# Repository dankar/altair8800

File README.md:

altair8800
==========

What is this?
-------------

What started as a Intel 8080 emulator turned into a Altair 8800 emulator with associated hardware for a front panel.

An updated version of this project is available at https://github.com/dankar/nanoaltair8800

Building
--------

The build for Arduino Uno is the most up to date. It should work to run "./build" and then "make && upload" in the arduino folder to compile and program.

arduino-mk is used by the makefile.

The code will look for certain files on the SD card. "88dskrom.bin" is a disk bootloader which will be loaded to offset 0xff00 in memory. "disk1.bin" and "disk2.bin" will be used by the 88-DCDD emulator and will act as disk 1 and disk 2 respectively.

Completeness
------------

Passes Kelly Smith test and cputest.com. Runs CP/M and all kinds of BASIC I could find. Altair DOS not working for some reason (complains about insufficient memory). Support for 88-DCDD. No tape or cassette.

There are probably still a few bugs that needs ironing out.

The performance is pretty poor. The emulator runs a couple of times slower than an original Altair 8800 which is a bit disappointing. It's of course also possible porting it to a faster MCU with more memory. Higher optimization levels will cause the code not to fit on an atmega328 but there are still code optimizations to be done. It is currently not possible to stop execution once started with the RUN/STOP switch. It's way too slow to check the front panel switches for each main loop.

Hardware
--------

A front panel has been designed and is available as a KiCad project under the PCB folder. The front panel is basically a bunch of shift registers for input from the switches and output to the LEDs, as well as a 23LC1024 SPI SRAM chip for memory and a MicroSD reader. Everything is attached on the SPI bus to the Arduino.

Known bugs
----------

The current hardware implementation has a bug in the MicroSD card holder-area. The pins are connected as they should be for a regular size SD card and not a MicroSD. If you want to use the panel with a MicroSD card you need to fix this.

Raspberry Pi
------------

The current code in the repo now supports running on Raspberry Pi instead of Arduino. This means that the MicroSD slot is not necessary any more, as well as the SRAM chip. The code runs faster on a Raspberry Pi as well. I would recommend this route for anyone interested in their own panel.

Todo
----

* Separate the Intel 8080 emulator and the Altair 8800 hardware emulation. E.g. make the port IO more abstract instead of Altair 8800 specific.
* Optimizations
* RUN/STOP switch enabled when running

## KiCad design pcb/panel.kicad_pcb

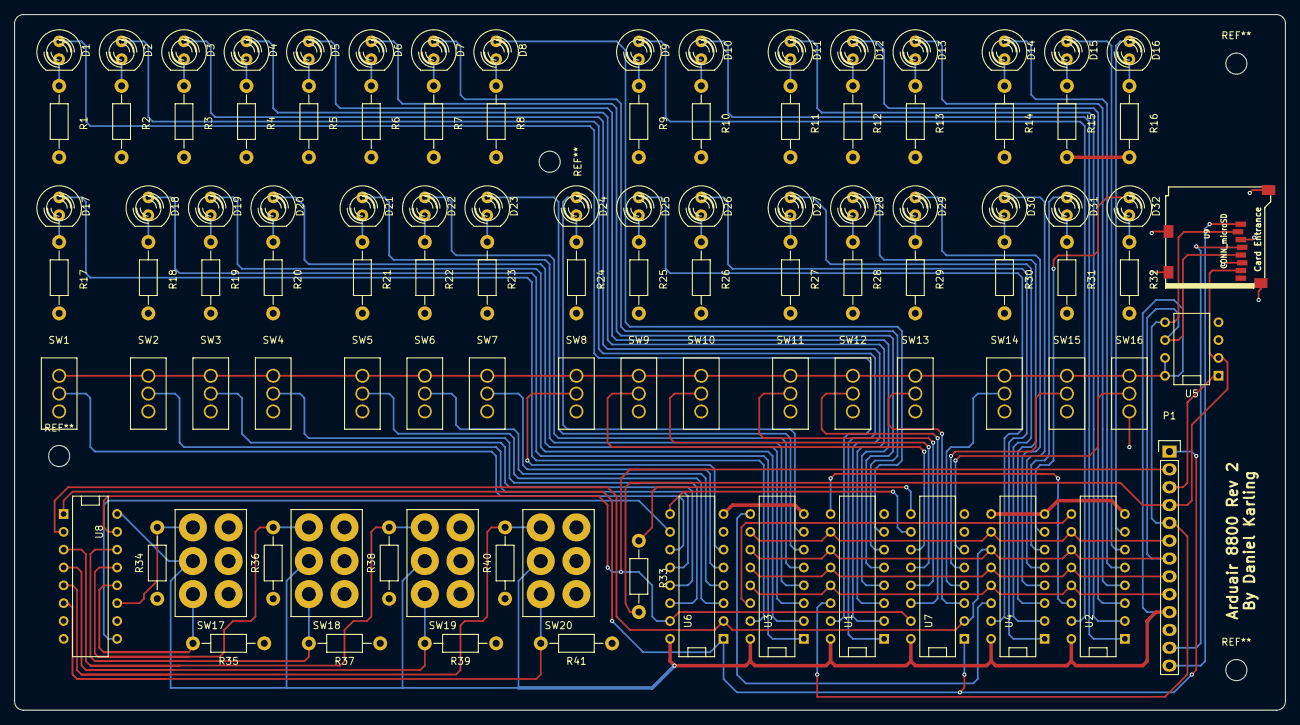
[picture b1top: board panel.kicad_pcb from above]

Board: 2 copper layers, 181.0 x 99.1 mm, 103 parts (0 on the bottom side), 107 nets.

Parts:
D1, D2, D3, D4, D5, D6, D7, D8, D9, D10, D11, D12, D13, D14, D15, D16, D17, D18, D19, D20, D21, D22, D23, D24, D25, D26, D27, D28, D29, D30, D31, D32: LED; LED-5MM
P1: CONN_01X09; Pin_Header_Straight_1x13
R1, R2, R3, R4, R5, R6, R7, R8, R9, R10, R11, R12, R13, R14, R15, R16, R17, R18, R19, R20, R21, R22, R23, R24, R25, R26, R27, R28, R29, R30, R31, R32, R33: 220R; Resistor_Horizontal_RM10mm
R34, R35, R36, R37, R38, R39, R40, R41: 10K; Resistor_Horizontal_RM10mm
SW1, SW2, SW3, SW4, SW5, SW6, SW7, SW8, SW9, SW10, SW11, SW12, SW13, SW14, SW15, SW16: SWITCH_INV; SwitchOnOn
SW17, SW18, SW19, SW20: SP3T; SwitchOnOffOn
U1, U2, U3, U4: 74HC595; DIP-16__300
U5: 23LC1024; DIP-8__300
U6, U7, U8: 74LS165; DIP-16__300
U9: CONN_microSD; Memory_Card_microSD_3M_290805

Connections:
/CLK: P1.7, U1.11, U2.11, U3.11, U4.11, U5.6, U6.2, U7.2, U8.2, U9.5
/LA1: D1.1, U1.15
/LA2: D2.1, U1.1
/LA3: D3.1, U1.2
/LA4: D4.1, U1.3
/LA5: D5.1, U1.4
/LA6: D6.1, U1.5
/LA7: D7.1, U1.6
/LA8: D8.1, U1.7
/LB1: D9.1, U2.15
/LB2: D10.1, U2.1
/LB3: D11.1, U2.2
/LB4: D12.1, U2.3
/LB5: D13.1, U2.4
/LB6: D14.1, U2.5
/LB7: D15.1, U2.6
/LB8: D16.1, U2.7
/LC1: D17.1, U3.15
/LC2: D18.1, U3.1
/LC3: D19.1, U3.2
/LC4: D20.1, U3.3
/LC5: D21.1, U3.4
/LC6: D22.1, U3.5
/LC7: D23.1, U3.6
/LC8: D24.1, U3.7
/LD1: D25.1, U4.15
/LD2: D26.1, U4.1
/LD3: D27.1, U4.2
/LD4: D28.1, U4.3
/LD5: D29.1, U4.4
/LD6: D30.1, U4.5
/LD7: D31.1, U4.6
/LD8: D32.1, U4.7
/LEDSTORE: P1.8, U1.12, U2.12, U3.12, U4.12
/MEM_CS: P1.3, U5.1
/MISO: P1.4, R33.2, U5.2, U9.7
/MOSI: P1.5, U1.14, U5.5, U9.2
/MR: P1.6, U1.10, U2.10, U3.10, U4.10
/OE: P1.9, U1.13, U2.13, U3.13, U4.13
/SD_SC: P1.13, U9.1
/SWA1: SW1.2, U6.11
/SWA2: SW2.2, U6.12
/SWA3: SW3.2, U6.13
/SWA4: SW4.2, U6.14
/SWA5: SW5.2, U6.3
/SWA6: SW6.2, U6.4
/SWA7: SW7.2, U6.5
/SWA8: SW8.2, U6.6
/SWB1: SW9.2, U7.11
/SWB2: SW10.2, U7.12
/SWB3: SW11.2, U7.13
/SWB4: SW12.2, U7.14
/SWB5: SW13.2, U7.3
/SWB6: SW14.2, U7.4
/SWB7: SW15.2, U7.5
/SWB8: SW16.2, U7.6
/SWC1: R34.1, SW17.1, U8.11
/SWC2: R35.1, SW17.4, U8.12
/SWC3: R36.1, SW18.1, U8.13
/SWC4: R37.1, SW18.4, U8.14
/SWC5: R38.1, SW19.1, U8.3
/SWC6: R39.1, SW19.4, U8.4
/SWC7: R40.1, SW20.1, U8.5
/SWC8: R41.1, SW20.4, U8.6
/SWITCH_CS: P1.2, U6.15, U7.15, U8.15
/SWITCH_LOAD: P1.1, U6.1, U7.1, U8.1
/VCC33: P1.12, U9.4
GND: P1.11, R1.2, R2.2, R3.2, R4.2, R5.2, R6.2, R7.2, R8.2, R9.2, R10.2, R11.2, R12.2, R13.2, R14.2, R15.2, R16.2, R17.2, R18.2, R19.2, R20.2, R21.2, R22.2, R23.2, R24.2, R25.2, R26.2, R27.2, R28.2, R29.2, R30.2, R31.2, R32.2, R34.2, R35.2, R36.2, R37.2, R38.2, R39.2, R40.2, R41.2, SW1.1, SW2.1, SW3.1, SW4.1, SW5.1, SW6.1, SW7.1, SW8.1, SW9.1, SW10.1, SW11.1, SW12.1, SW13.1, SW14.1, SW15.1, SW16.1, U1.8, U2.8, U3.8, U4.8, U4.9, U5.3, U5.4, U6.7, U6.8, U7.7, U7.8, U8.7, U8.8, U8.10, U9.3, U9.6, U9.9
unnamed: D1.2, R1.1
unnamed: D2.2, R2.1
unnamed: D3.2, R3.1
unnamed: D4.2, R4.1
unnamed: D5.2, R5.1
unnamed: D6.2, R6.1
unnamed: D7.2, R7.1
unnamed: D8.2, R8.1
unnamed: D9.2, R9.1
unnamed: D10.2, R10.1
unnamed: D11.2, R11.1
unnamed: D12.2, R12.1
unnamed: D13.2, R13.1
unnamed: D14.2, R14.1
unnamed: D15.2, R15.1
unnamed: D16.2, R16.1
unnamed: D17.2, R17.1
unnamed: D18.2, R18.1
unnamed: D19.2, R19.1
unnamed: D20.2, R20.1
unnamed: D21.2, R21.1
unnamed: D22.2, R22.1
unnamed: D23.2, R23.1
unnamed: D24.2, R24.1
unnamed: D25.2, R25.1
unnamed: D26.2, R26.1
unnamed: D27.2, R27.1
unnamed: D28.2, R28.1
unnamed: D29.2, R29.1
unnamed: D30.2, R30.1
unnamed: D31.2, R31.1
unnamed: D32.2, R32.1
unnamed: R33.1, U7.9
unnamed: U1.9, U2.14
unnamed: U2.9, U3.14
unnamed: U3.9, U4.14
unnamed: U6.9, U7.10
unnamed: U6.10, U8.9
VCC: P1.10, SW1.3, SW2.3, SW3.3, SW4.3, SW5.3, SW6.3, SW7.3, SW8.3, SW9.3, SW10.3, SW11.3, SW12.3, SW13.3, SW14.3, SW15.3, SW16.3, SW17.3, SW18.3, SW19.3, SW20.3, U1.16, U2.16, U3.16, U4.16, U5.7, U5.8, U6.16, U7.16, U8.16

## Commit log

2014-12-15 Initial
2014-12-15 Linux
2014-12-15 Fixed some bugs
2014-12-15 Reverted some changes
2014-12-15 Added VS files to .gitignore
2014-12-15 Added visual studio solution
2014-12-15 Some more files to .gitignore
2014-12-16 Non blocking socket on linux
2014-12-16 Make sure we return the correct value on unused IO ports
2014-12-16 Added ifdef on socket blocking
2014-12-16 Slight cleanup of linux code
2014-12-17 Optimizations
2014-12-17 Memory is now accessed through callbacks
2014-12-17 New .gitignore for the arduino folder since we need to copy files
2014-12-17 Added arduino stuff
2014-12-18 Arduino build now runs CP/M
2014-12-18 Debugging and new disk boot loader
2014-12-20 sdasdsa
2015-01-05 Changed arduino code to use 23LC1024 SRAM chip instead of SD card for memory.
2015-01-05 Added build script for arduino
2015-01-05 Fixed 2sio so that ladder.com and zork works
2015-01-05 Added optional debug outputs for disk driver and fixed issue with integer overflow wheen changing tracks.
2015-01-06 Clean-up
2015-01-06 Moved memory access to inline functions
2015-01-06 Fixed build for x86
2015-01-06 Removed old server.py
2015-01-06 Divisor
2015-03-28 asdf
2015-04-12 Added schematics
2015-04-12 Changed value of R33 to 220 Ohms. New value found through testing.
2015-04-12 Added support for the hardware front panel.
2015-04-13 Updated VS build
2016-03-12 Added support for panel connected to Raspberry Pi. Regular Linux builds now target Raspberry Pi.
2016-03-17 Final parts of panel support on Raspberry Pi.
2016-11-11 Update README.md
    Added the current status of the project to readme.
